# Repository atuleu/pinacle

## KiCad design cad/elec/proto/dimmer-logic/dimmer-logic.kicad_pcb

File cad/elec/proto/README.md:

# Struvcture of the prototypes

We should ahve three prototype here :

#  Dimmer board

The puropose of this board is to provide the High side, non isolated PWM chopping.

  * Use 4 mosfet to do PWM AC chopping
  * Non isolated of main, has a floating ground with internal +12V referenced to it using a SR087 device
  * Prepared to have filtering element (before and after main)
  * Mosfet driver are Adum3325 / 4325

Inputs :

* Non isolated :
  * AC main, non isolated
* Isolated :
  * Logic GND
  * +VCC 5v
  * commutation pattern NH, NL, LH, LL ({Neutral,Phase} {High,Low} switch)

Outputs :
* Non Isolated :
  * AC load 
	
Use same length for the 4 signal pair

Do not forget to add space for filtering element on the prototype

# AC-DC converter with phase detection and Microntroller

Provide a stable 5V supply, and a PIC that computes the driving signals

Inputs :
* Non isolated :
  * AC main
* Isolated
  * GND
  * Signal +5V
  * 
Outputs isolated :
  * Logic GND
  * +5V
  * NH, NL, LH, LL

Some computations. We want a 500mA regulated output using 7805. So we want at least a volatge of 7V

We use a 230 Vrms -> 9 Vrms converter, so the peak voltage is 11.45 - 14.07 if we use standard 1n4001 diode, we will have at 2A peak current, a forward voltage of 0.9V,

So we get for the ripple voltage :

v_ripple = 11.45 -2 -7 = 2.45

so the filter capacitor is :

C = dt * I_load / v_ripple

C=  8ms * 500 mA / 2.45 = 1600 uF we choose a standard 1500uF capacitior

Diode selection, fromk ltspice, we have more than 1A Rms current, we use a 2A rated diode bridge 1N5062 seems good

Startup peak is above 20 Amp, but the diode can witstands at least 60A

we use a 7805 for the regulation

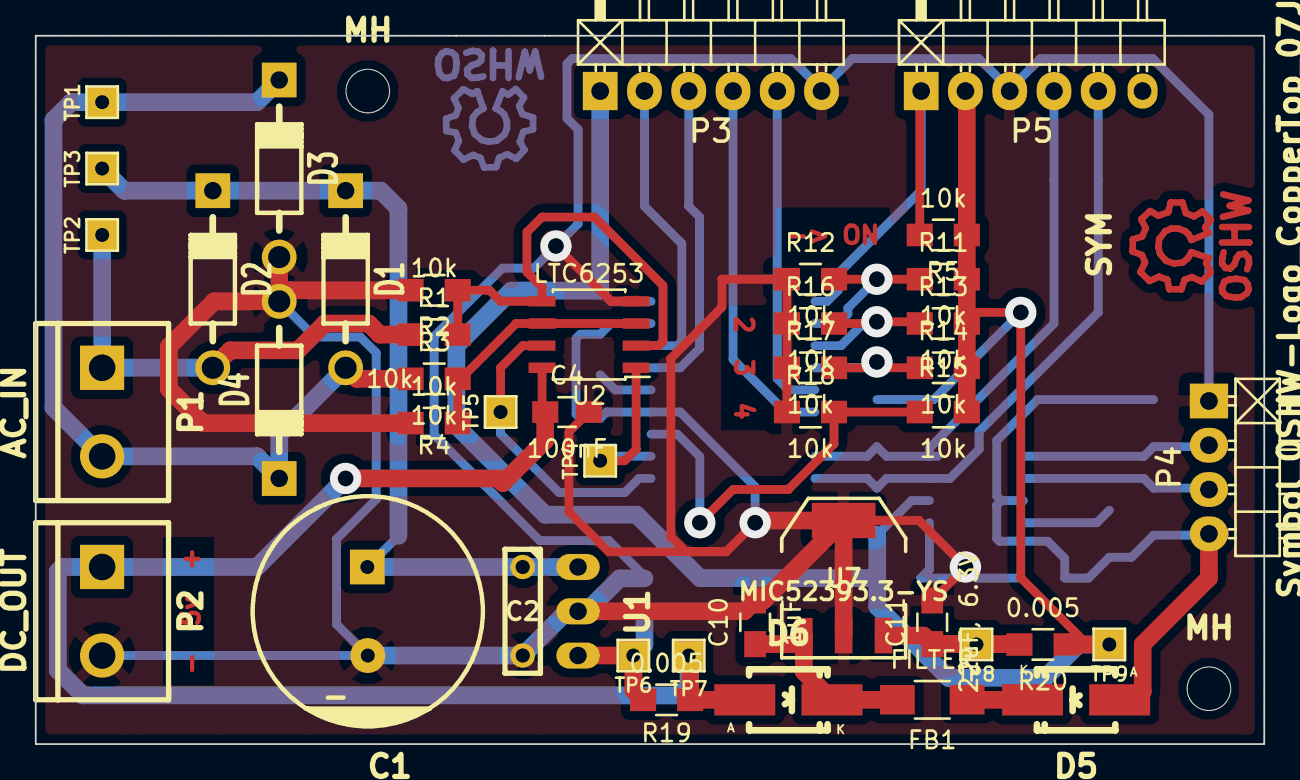
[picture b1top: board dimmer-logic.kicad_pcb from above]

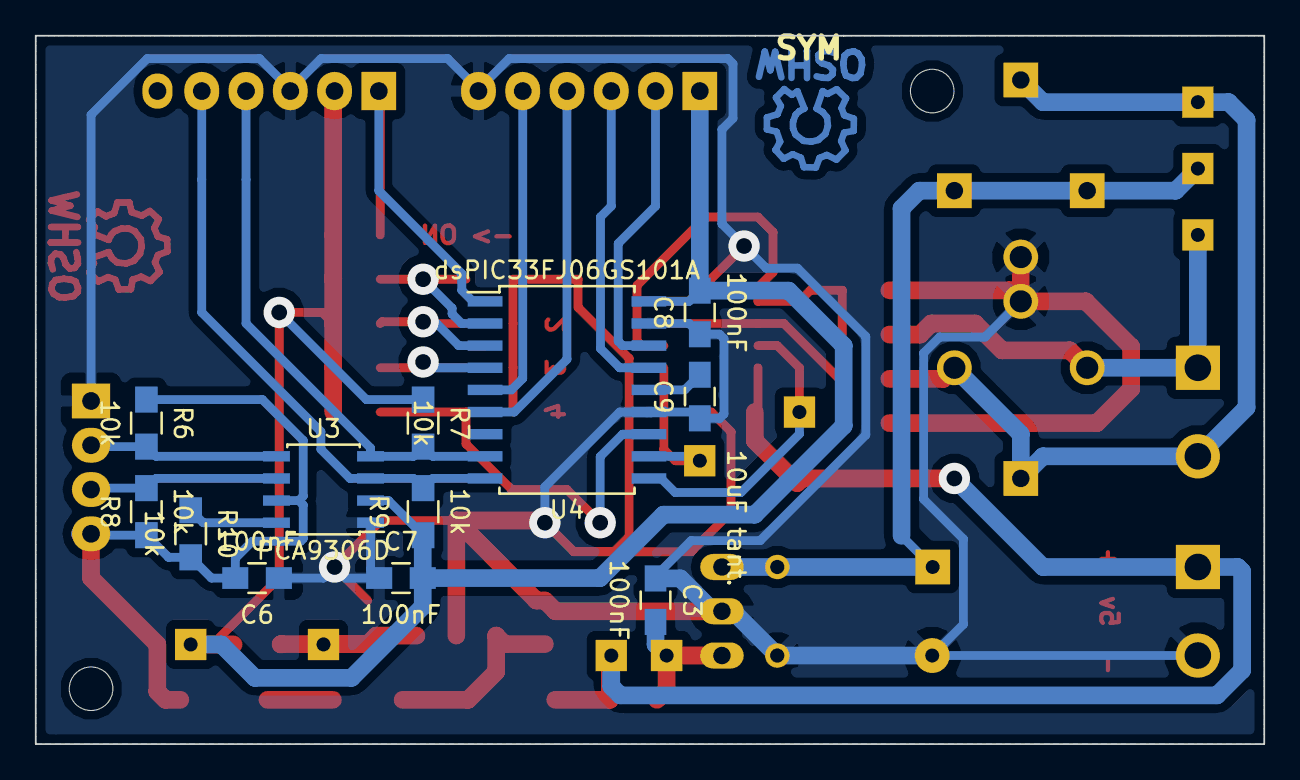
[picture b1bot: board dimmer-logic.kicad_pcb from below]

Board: 2 copper layers, 70.5 x 40.6 mm, 60 parts (13 on the bottom side), 30 nets.

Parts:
C1: 1500uF, 25V; Capacitor13x25RM2.5
C2: 330nF; C2
C3, C4, C6, C7, C8: 100nF; C_0805_HandSoldering
C9: 10uF tant.; C_0805_HandSoldering
C10: 1uF; C_0805_HandSoldering
C11: 22uF, 6.3V; C_0805_HandSoldering
D1, D2, D3, D4: 1N5062; Diode_DO-41_SOD81_Horizontal_RM10
D5, D6: DIODESCH; Diode-SMA_Handsoldering
FB1: FILTER; R_1206_HandSoldering
MH: MountingHole_2-5mm_RevA_Date21Jun2010; MountingHole_2-5mm
MH#2: MountingHole_2-5mm_RevA_Date21Jun2010; MountingHole_2-5mm
P1: AC_IN; bornier2
P2: DC_OUT; bornier2
P3: LOGIC_OUT; Pin_Header_Angled_1x06
P4: I2C_BUS; Pin_Header_Angled_1x04
P5: dsPIC_PGM; Pin_Header_Angled_1x06
R1, R2, R3, R4, R5, R6, R7, R8, R9, R10, R11, R12, R13, R14, R15, R16, R17, R18: 10k; R_0805_HandSoldering
R19, R20: 0.005; R_0805_HandSoldering
SYM: Symbol_OSHW-Logo_CopperTop_07Jul2012; Symbol_OSHW-Logo_CopperTop
SYM#2: Symbol_OSHW-Logo_CopperTop_07Jul2012; Symbol_OSHW-Logo_CopperTop
TP1: L; SIL-1
TP2: N; SIL-1
TP3: RED; SIL-1
TP4: DET_L; SIL-1
TP5: DET_N; SIL-1
TP6: 5VA; SIL-1
TP7: 5VB; SIL-1
TP8: 3v3A; SIL-1
TP9: 3v3B; SIL-1
U1: LM7805CT; TO-220_Neutral123_PadsOnly
U2: LTC6253; SOIC-8_3.9x4.9mm_Pitch1.27mm
U3: PCA9306D; SOIC-8_3.9x4.9mm_Pitch1.27mm
U4: dsPIC33FJ06GS101A; SOIC-18_7.5x11.6mm_Pitch1.27mm
U7: MIC52393.3-YS; SOT-223

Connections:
+3.3V: C7.1, C8.1, P3.1, P5.2, R5.1, R7.2, R9.2, R11.2, R13.2, R14.2, R15.2, R20.1, TP9.1, U3.2, U4.18
+5V: C4.1, D6.1, P2.1, R19.1, TP7.1, U2.8
/ac_dc_supply/IN_RED: C1.1, C2.1, D1.2, D2.2, TP3.1, U1.1
/ac_dc_supply/LM_OUT: C3.1, R19.2, TP6.1, U1.3
/ac_dc_supply/l_in: D1.1, D3.2, D4.2, P1.2, R3.1, TP1.1
/ac_dc_supply/l_low: R3.2, R4.1, U2.3, U2.6
/ac_dc_supply/n_in: D2.1, P1.1, R1.1, TP2.1
/ac_dc_supply/n_low: R1.2, R2.1, U2.2, U2.5
/dsPIC/3v3_supply/5v_in: C10.1, D6.2, FB1.2, U7.1
/dsPIC/5V_BUS: C6.1, D5.1, P4.4, R6.2, R8.2, R10.1, U3.7
/dsPIC/ADDR1: R11.1, R12.2, U4.2
/dsPIC/ADDR2: R13.1, R16.2, U4.3
/dsPIC/ADDR3: R14.1, R17.2, U4.4
/dsPIC/ADDR4: R15.1, R18.2, U4.12
/dsPIC/SCL_BUS: P4.3, R8.1, U3.6
/dsPIC/SCL_UC: P5.5, R9.1, U3.3, U4.9
/dsPIC/SDA_BUS: P4.2, R6.1, U3.5
/dsPIC/SDA_UC: P5.4, R7.1, U3.4, U4.8
/dsPIC/ac_phase_+: TP4.1, U2.1, U4.11
/dsPIC/ac_phase_-: TP5.1, U2.7, U4.10
/dsPIC/lh: P3.3, U4.15
/dsPIC/ll: P3.2, U4.16
/dsPIC/nh: P3.4, U4.6
/dsPIC/nl: P3.5, U4.5
/dsPIC/~MCLR: P5.1, R5.2, U4.1
GND: C1.2, C2.2, C3.2, C4.2, C6.2, C7.2, C8.2, C9.2, C10.2, C11.2, D3.1, D4.1, P2.2, P3.6, P4.1, P5.3, R2.2, R4.2, R12.1, R16.1, R17.1, R18.1, U1.2, U2.4, U3.1, U4.13, U4.17, U7.2, U7.4
unnamed: C9.1, U4.14
unnamed: C11.1, R20.2, TP8.1, U7.3
unnamed: D5.2, FB1.1
unnamed: R10.2, U3.8

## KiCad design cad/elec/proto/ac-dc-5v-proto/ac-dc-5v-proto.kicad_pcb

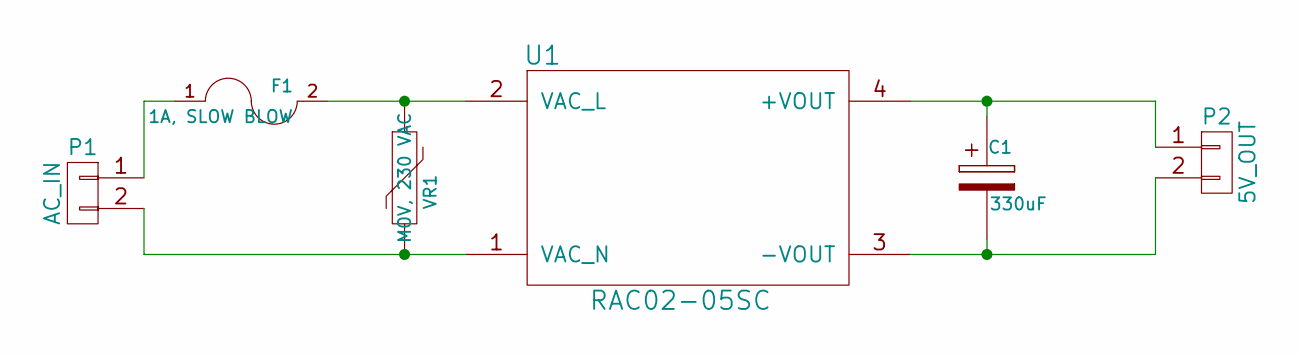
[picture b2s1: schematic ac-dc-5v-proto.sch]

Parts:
C1: 330uF; Capacitor10x13RM5
F1: 1A, SLOW BLOW; Fuseholder5x20_horiz_SemiClosed_Casing10x25mm
P1: AC_IN; bornier2
P2: 5V_OUT; bornier2
U1: RAC02-05SC; RAC0X-C
VR1: MOV, 230 VAC; R3

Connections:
unnamed: C1.1, P2.1, U1.4 (+VOUT)
unnamed: C1.2, P2.2, U1.3 (-VOUT)
unnamed: F1.1, P1.1
unnamed: F1.2, U1.2 (VAC_L), VR1.1
unnamed: P1.2, U1.1 (VAC_N), VR1.2

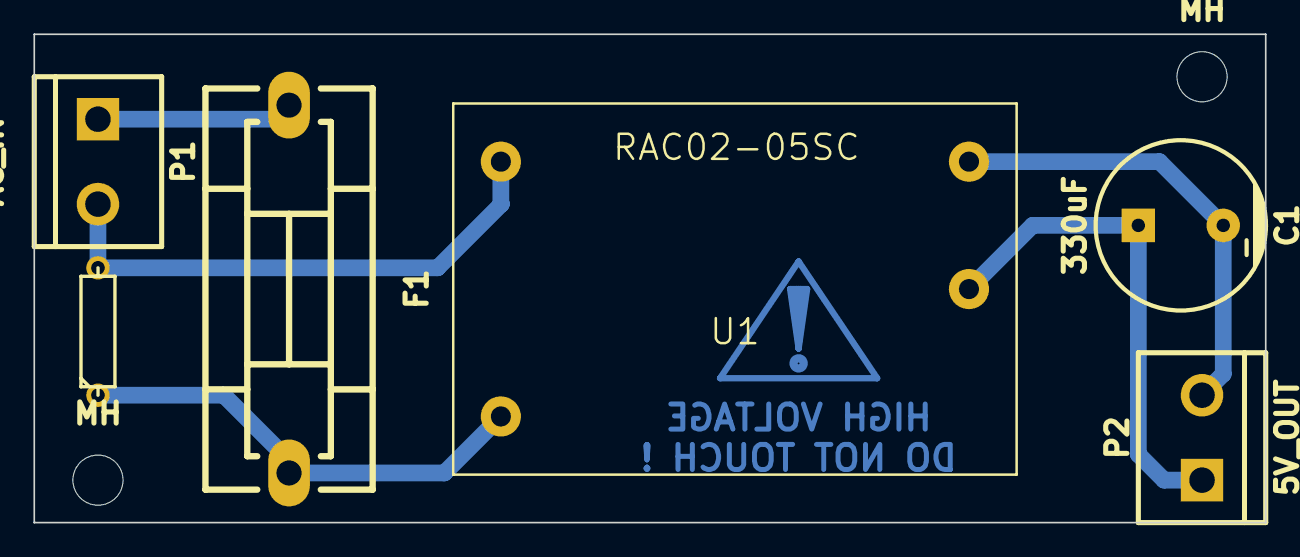
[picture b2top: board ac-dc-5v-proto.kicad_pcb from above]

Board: 2 copper layers, 73.7 x 29.2 mm, 9 parts (1 on the bottom side), 5 nets.

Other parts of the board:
MH: MountingHole_3mm_RevA_Date21Jun2010; MountingHole_3mm
MH#2: MountingHole_3mm_RevA_Date21Jun2010; MountingHole_3mm
Sym: Symbol_Attention_CopperTop_Small

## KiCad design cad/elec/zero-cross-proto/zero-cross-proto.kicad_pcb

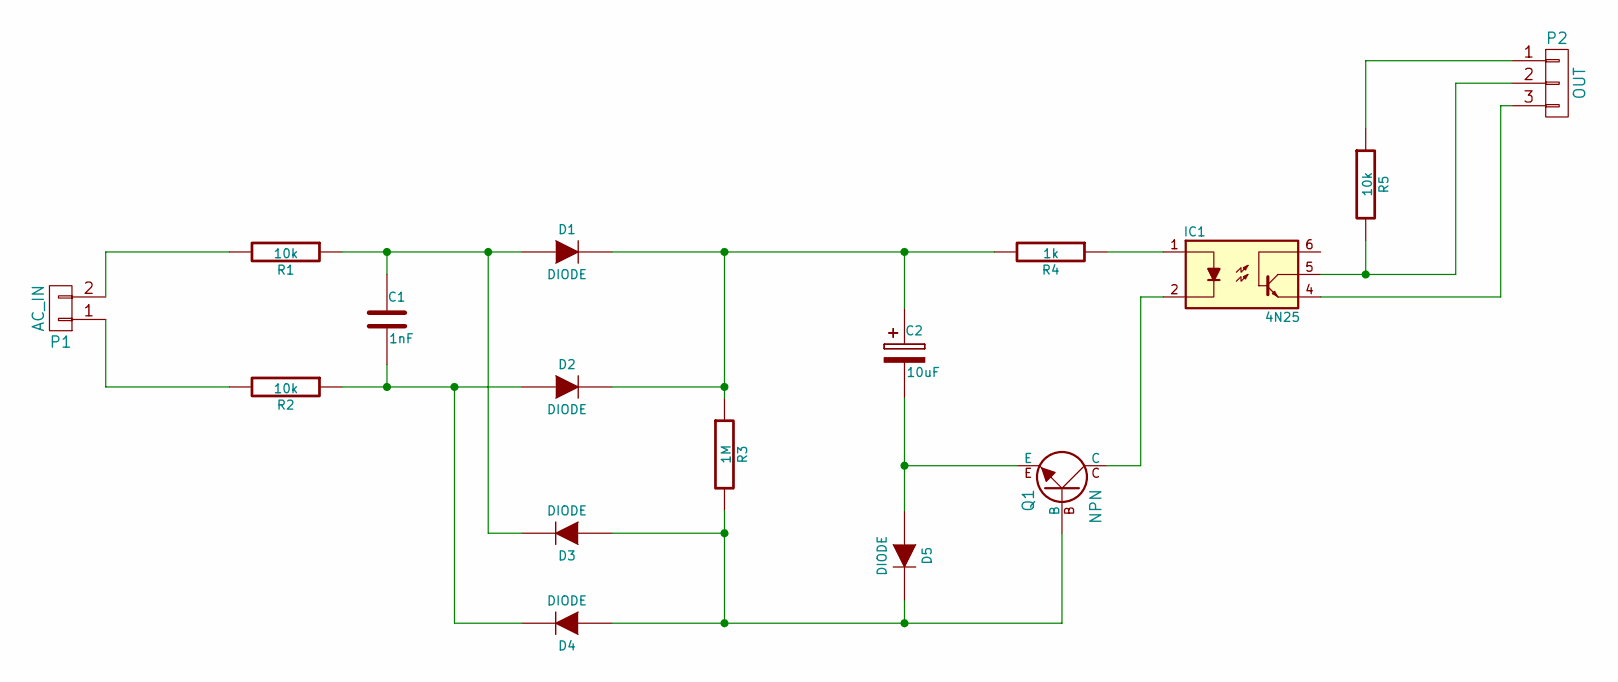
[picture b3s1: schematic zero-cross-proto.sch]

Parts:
C1: 1nF; Capacitor5x11RM2.5
C2: 10uF; Capacitor5x11RM2.5
D1, D2, D3, D4, D5: DIODE; Diode_DO-35_SOD27_Horizontal_RM10
IC1: 4N25; DIP-6__300_ELL
P1: AC_IN; bornier2
P2: OUT; bornier3
Q1: NPN; TO-92-Bipolar-inline-wide-EBC
R1, R2, R5: 10k; Resistor_Horizontal_RM10mm
R3: 1M; Resistor_Horizontal_RM10mm
R4: 1k; Resistor_Horizontal_RM10mm

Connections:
unnamed: C1.1, D1.1 (A), D3.2 (K), R1.1
unnamed: C1.2, D2.1 (A), D4.2 (K), R2.1
unnamed: C2.1, D1.2 (K), D2.2 (K), R3.1, R4.2
unnamed: C2.2, D5.1 (A), Q1.E
unnamed: D3.1 (A), D4.1 (A), D5.2 (K), Q1.B, R3.2
unnamed: IC1.1, R4.1
unnamed: IC1.2, Q1.C
unnamed: IC1.4, P2.3
unnamed: IC1.5, P2.2, R5.2
unnamed: P1.1, R2.2
unnamed: P1.2, R1.2
unnamed: P2.1, R5.1

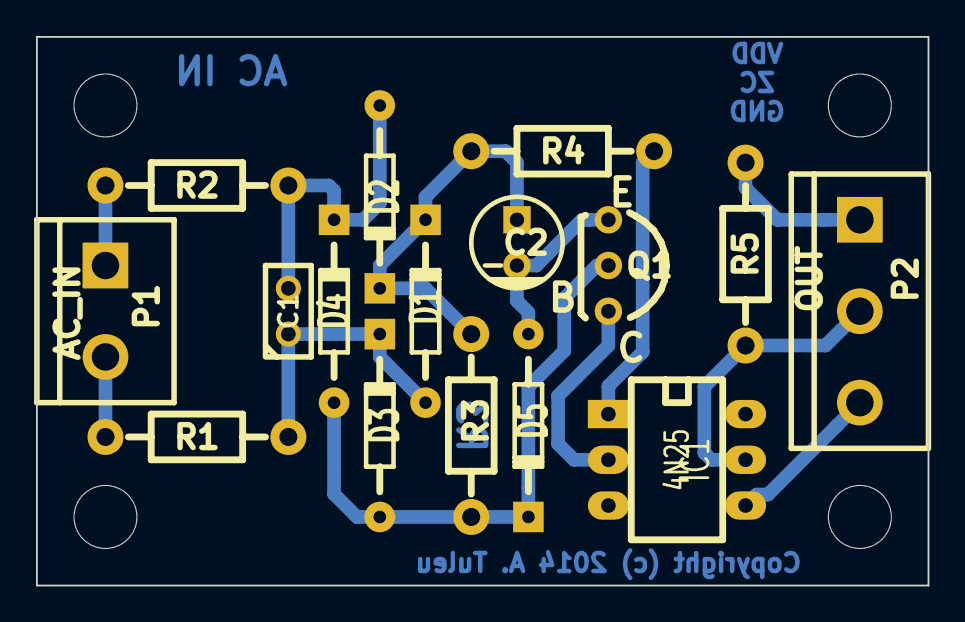
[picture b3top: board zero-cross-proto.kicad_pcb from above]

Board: 2 copper layers, 49.5 x 30.5 mm, 20 parts (0 on the bottom side), 12 nets.

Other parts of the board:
MH: MountingHole_3-5mm_RevA_Date21Jun2010; MountingHole_3-5mm
MH#2, MH#3, MH#4: MountingHole_3-5mm_RevA_Date21Jun2010; MountingHole_3-5mm

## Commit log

2014-10-13 Adds a README.md
2014-10-14 Adds some documentation for the project
2014-10-14 More biblio
2014-10-14 Adds a license
2014-10-14 Adds a dimmer prototype project
2014-10-15 Update biblio.md
    Adds a resource on evaluation board
2014-10-17 Adds a prototype for zero-crossing detector
2014-10-17 Moves to proto
2014-10-17 Adds libs for recom parts
2014-10-17 Adds ac-dc-5V transformer prototype
2014-10-29 Adds dimmer proto
2014-10-29 Plan for furture development
2014-10-29 Adds more info on design guidelines
2014-10-29 Adds new devices libraries
2014-10-29 Starts schematics for the logic side
2014-11-03 Adds a first prototype layout for dimmer-logic
2014-11-03 Adds all references

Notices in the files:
cad/elec/zero-cross-proto/zero-cross-proto.kicad_pcb:
Copyright (c) 2014 A. Tuleu
